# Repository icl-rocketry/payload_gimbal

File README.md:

# payload_gimbal
the ReAL payload

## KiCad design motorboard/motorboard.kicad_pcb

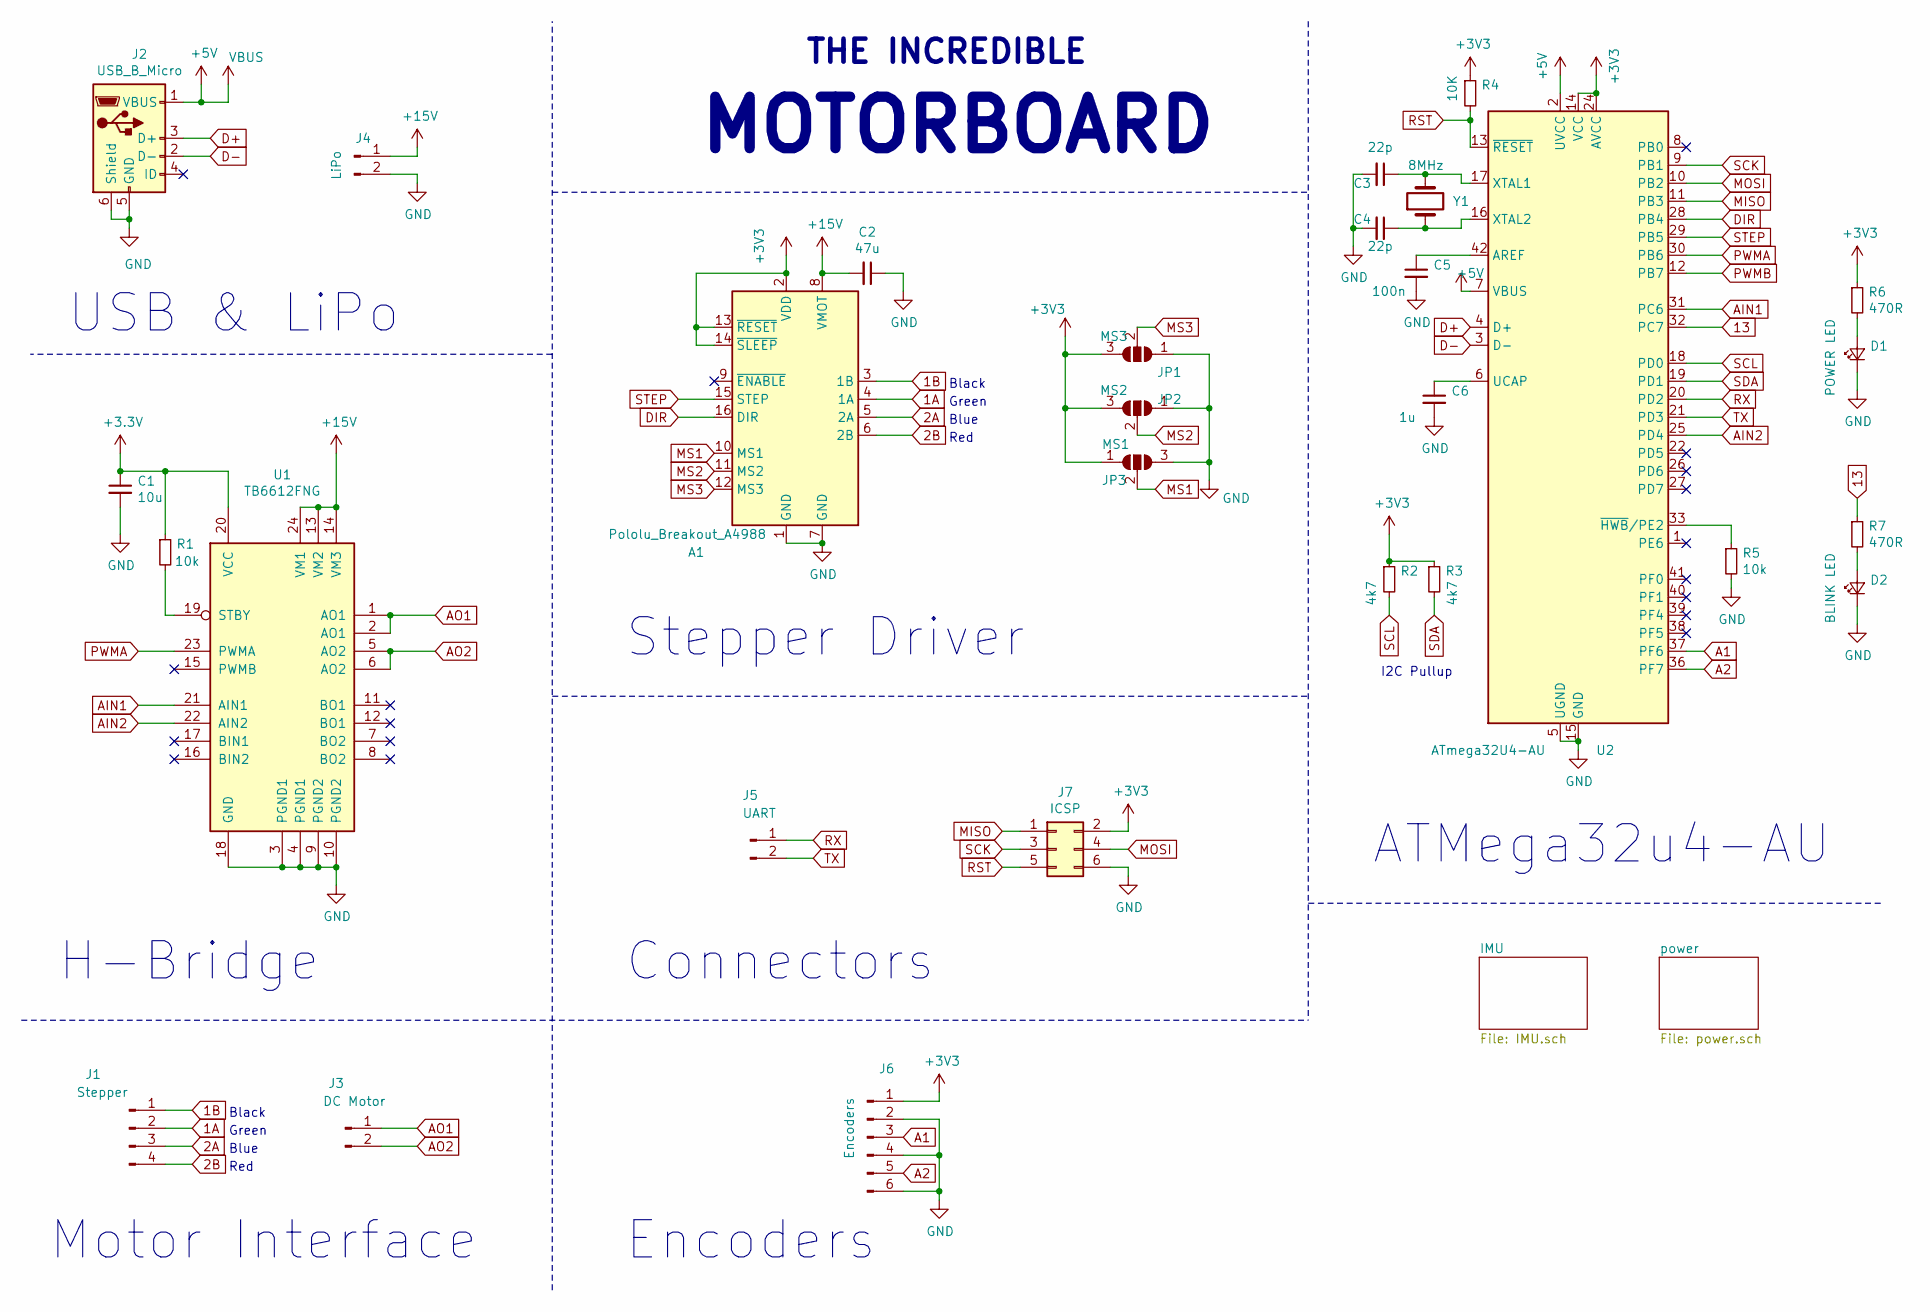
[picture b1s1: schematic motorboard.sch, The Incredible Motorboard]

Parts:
A1: Pololu_Breakout_A4988; Pololu_Breakout-16_15.2x20.3mm
C1: 10u; C_0603_1608Metric
C2: 47u; C_0603_1608Metric
C3, C4: 22p; C_0603_1608Metric
C5: 100n; C_0603_1608Metric
C6: 1u; C_0603_1608Metric
D1: POWER LED; D_0603_1608Metric_Castellated
D2: BLINK LED; D_0603_1608Metric_Castellated
J1: Stepper; PinHeader_1x06_P2.54mm_Vertical
J2: USB_B_Micro; USB_Micro-B_Molex-105017-0001
J3: DC Motor; PinHeader_1x02_P2.54mm_Vertical
J4: LiPo; AMASS_XT30UPB-F_1x02_P5.0mm_Vertical
J5: UART; PinHeader_1x02_P2.54mm_Vertical
J6: Encoders; PinHeader_1x06_P2.54mm_Vertical
J7: ICSP; PinHeader_2x03_P2.54mm_Vertical
JP1: MS3; SolderJumper-3_P1.3mm_Open_RoundedPad1.0x1.5mm_NumberLabels
JP2: MS2; SolderJumper-3_P1.3mm_Open_RoundedPad1.0x1.5mm_NumberLabels
JP3: MS1; SolderJumper-3_P1.3mm_Open_RoundedPad1.0x1.5mm_NumberLabels
R1, R5: 10k; R_0603_1608Metric
R2, R3: 4k7; R_0603_1608Metric
R4: 10K; R_0603_1608Metric
R6, R7: 470R; R_0603_1608Metric
U1: TB6612FNG; SSOP-24_5.3x8.2mm_P0.65mm
U2: ATmega32U4-AU; TQFP-44_10x10mm_P0.8mm
Y1: 8MHz; Crystal_HC49-4H_Vertical

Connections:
1A: A1.4 (1A), J1.2
1B: A1.3 (1B), J1.1
2A: A1.5 (2A), J1.3
2B: A1.6 (2B), J1.4
13: R7.1, U2.32 (PC7)
+5V: J2.1 (VBUS), U2.2 (UVCC), U2.7 (VBUS); also elsewhere on the board
+15V: A1.8 (VMOT), C2.2, J4.1, U1.13 (VM2), U1.14 (VM3), U1.24 (VM1); also elsewhere on the board
A1: J6.3, U2.37 (PF6)
A2: J6.5, U2.36 (PF7)
AIN1: U1.21 (AIN1), U2.31 (PC6)
AIN2: U1.22 (AIN2), U2.25 (PD4)
AO1: J3.1, U1.1 (AO1), U1.2 (AO1)
AO2: J3.2, U1.5 (AO2), U1.6 (AO2)
D+: J2.3 (D+), U2.4 (D+)
D-: J2.2 (D-), U2.3 (D-)
DIR: A1.16 (DIR), U2.28 (PB4)
GND: A1.1 (GND), A1.7 (GND), C1.2, C2.1, C3.2, C4.2, C5.2, C6.2, D1.1 (K), D2.1 (K), J2.5 (GND), J2.6 (Shield), J4.2, J6.2, J6.4, J6.6, J7.6, JP1.1 (A), JP2.1 (A), JP3.3 (B), R5.2, U1.3 (PGND1), U1.4 (PGND1), U1.9 (PGND2), U1.10 (PGND2), U1.18 (GND), U2.5 (UGND), U2.15 (GND), U2.23 (GND), U2.35 (GND), U2.43 (GND); also elsewhere on the board
MISO: J7.1, U2.11 (PB3)
MOSI: J7.4, U2.10 (PB2)
MS1: A1.10 (MS1), JP3.2 (C)
MS2: A1.11 (MS2), JP2.2 (C)
MS3: A1.12 (MS3), JP1.2 (C)
unnamed: C3.1, U2.17 (XTAL1), Y1.2
unnamed: C4.1, U2.16 (XTAL2), Y1.1
unnamed: C5.1, U2.42 (AREF)
unnamed: C6.1, U2.6 (UCAP)
unnamed: D1.2 (A), R6.2
unnamed: D2.2 (A), R7.2
unnamed: R1.2, U1.19 (STBY)
unnamed: R5.1, U2.33 (~HWB~/PE2)
PWMA: U1.23 (PWMA), U2.30 (PB6)
PWMB: U2.12 (PB7)
RST: J7.5, R4.2, U2.13 (~RESET)
RX: J5.1, U2.20 (PD2)
SCK: J7.3, U2.9 (PB1)
SCL: R2.2, U2.18 (PD0); also elsewhere on the board
SDA: R3.2, U2.19 (PD1); also elsewhere on the board
STEP: A1.15 (STEP), U2.29 (PB5)
TX: J5.2, U2.21 (PD3)

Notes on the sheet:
H-Bridge
USB & LiPo
ATMega32u4-AU
Motor Interface
Encoders
MOTORBOARD
THE INCREDIBLE
I2C Pullup
Stepper Driver
Black
Green
Blue
Red
Connectors

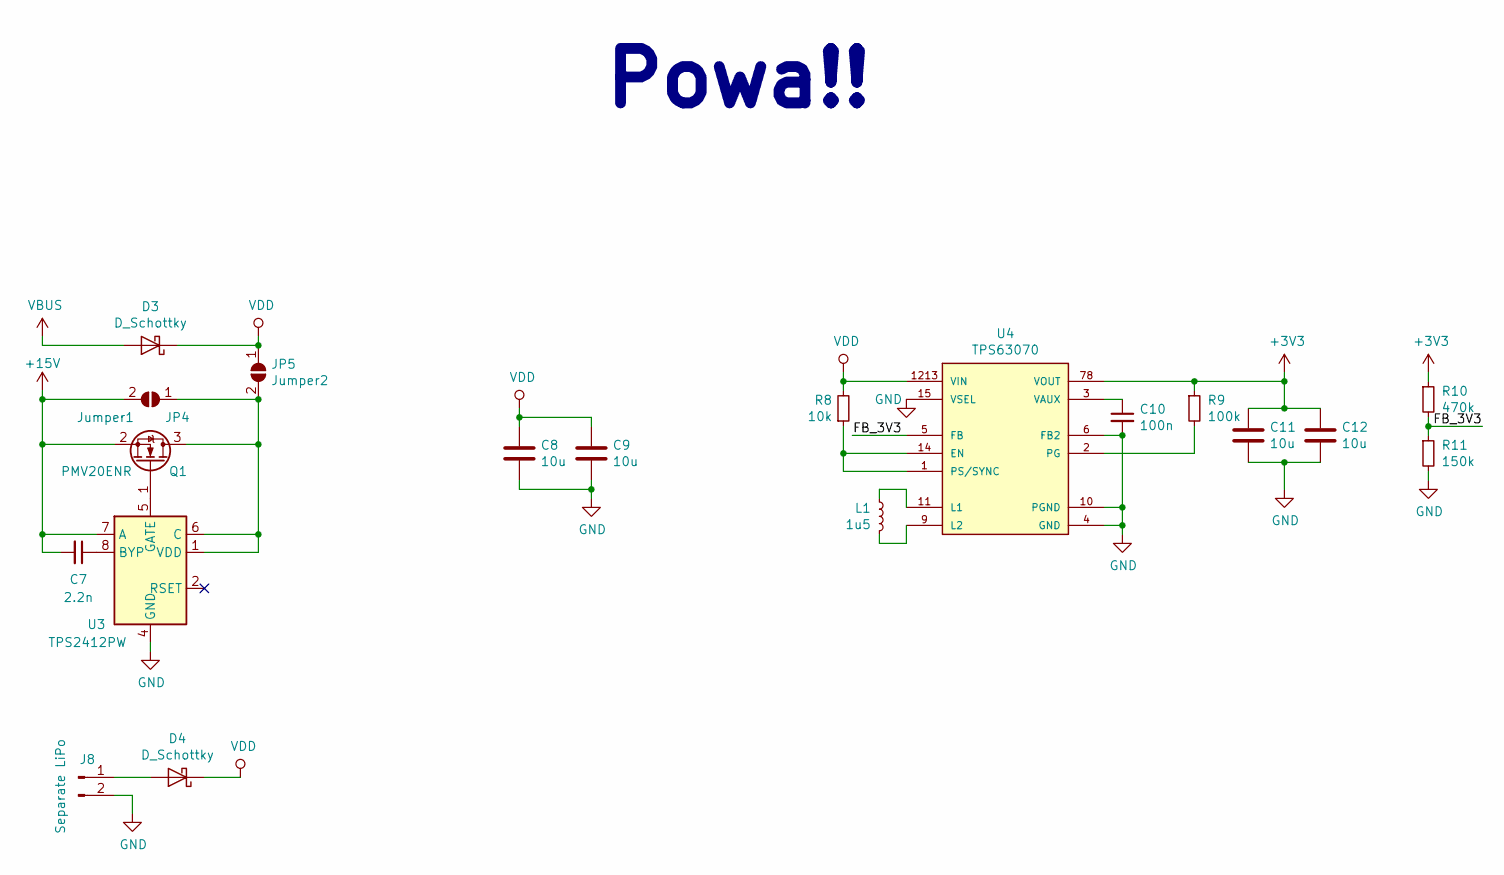
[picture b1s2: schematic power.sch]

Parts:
C7: 2.2n; C_0603_1608Metric
C8, C9, C11, C12: 10u; C_0603_1608Metric
C10: 100n; C_0603_1608Metric
D3, D4: D_Schottky; D_SOD-123F
J8: Separate LiPo; PinHeader_1x02_P2.54mm_Vertical
JP4: Jumper1; SolderJumper-2_P1.3mm_Open_RoundedPad1.0x1.5mm
JP5: Jumper2; SolderJumper-2_P1.3mm_Open_RoundedPad1.0x1.5mm
L1: 1u5; L_Taiyo-Yuden_NR-30xx
Q1: PMV20ENR; SOT-23
R8: 10k; R_0603_1608Metric
R9: 100k; R_0603_1608Metric
R10: 470k; R_0603_1608Metric
R11: 150k; R_0603_1608Metric
U3: TPS2412PW; TSSOP-8_4.4x3mm_P0.65mm
U4: TPS63070; Texas_PowerVFQFN_15

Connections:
+5V: D3.2 (A); also elsewhere on the board
+15V: C7.2, JP4.2 (B), Q1.2 (S), U3.7 (A); also elsewhere on the board
/power/FB_3V3: R10.2, R11.1, U4.5 (FB)
GND: C8.2, C9.2, C10.2, C11.2, C12.2, J8.2, R11.2, U3.3 (GND), U3.4 (GND), U4.4 (GND), U4.6 (FB2), U4.10 (PGND), U4.15 (VSEL); also elsewhere on the board
unnamed: C7.1, U3.8 (BYP)
unnamed: C10.1, U4.3 (VAUX)
unnamed: D4.2 (A), J8.1
unnamed: JP4.1 (A), JP5.2 (B), Q1.3 (D), U3.1 (VDD), U3.6 (C)
unnamed: L1.1, U4.9 (L2)
unnamed: L1.2, U4.11 (L1)
unnamed: Q1.1 (G), U3.5 (GATE)
unnamed: R8.1, U4.1 (PS/SYNC), U4.14 (EN)
unnamed: R9.2, U4.2 (PG)
VDD: C8.1, C9.1, D3.1 (K), D4.1 (K), JP5.1 (A), R8.2, U4.1213 (VIN)

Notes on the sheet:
Powa!!

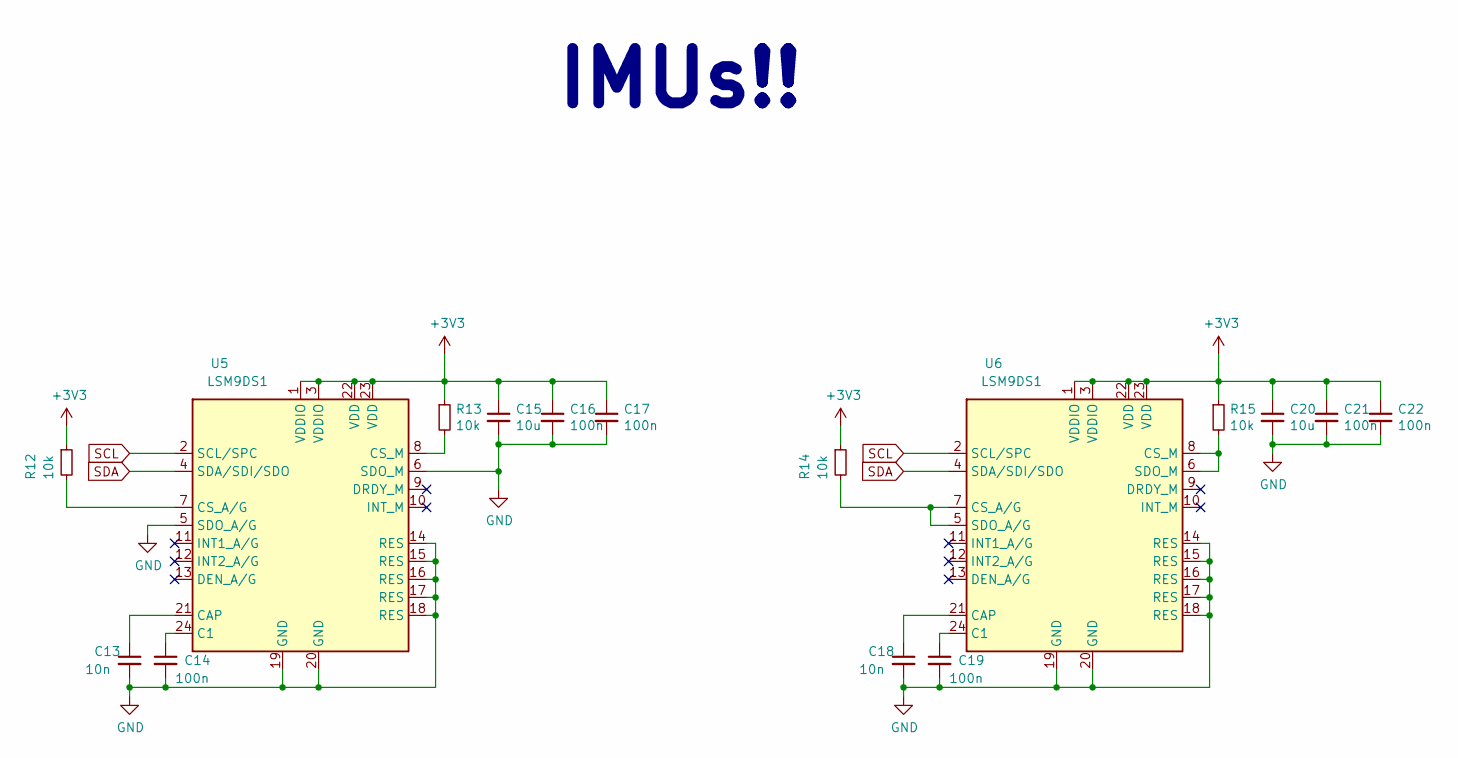
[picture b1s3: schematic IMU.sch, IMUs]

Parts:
C13, C18: 10n; C_0603_1608Metric
C14, C16, C17, C19, C21, C22: 100n; C_0603_1608Metric
C15, C20: 10u; C_0603_1608Metric
R12, R13, R14, R15: 10k; R_0603_1608Metric
U5, U6: LSM9DS1; LGA-24L_3x3.5mm_P0.43mm

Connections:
GND: C13.2, C14.2, C15.2, C16.2, C17.2, C18.2, C19.2, C20.2, C21.2, C22.2, U5.5 (SDO_A/G), U5.6 (SDO_M), U5.14 (RES), U5.15 (RES), U5.16 (RES), U5.17 (RES), U5.18 (RES), U5.19 (GND), U5.20 (GND), U6.14 (RES), U6.15 (RES), U6.16 (RES), U6.17 (RES), U6.18 (RES), U6.19 (GND), U6.20 (GND); also elsewhere on the board
unnamed: C13.1, U5.21 (CAP)
unnamed: C14.1, U5.24 (C1)
unnamed: C18.1, U6.21 (CAP)
unnamed: C19.1, U6.24 (C1)
unnamed: R12.2, U5.7 (CS_A/G)
unnamed: R13.2, U5.8 (CS_M)
unnamed: R14.2, U6.5 (SDO_A/G), U6.7 (CS_A/G)
unnamed: R15.2, U6.6 (SDO_M), U6.8 (CS_M)
SCL: U5.2 (SCL/SPC), U6.2 (SCL/SPC); also elsewhere on the board
SDA: U5.4 (SDA/SDI/SDO), U6.4 (SDA/SDI/SDO); also elsewhere on the board

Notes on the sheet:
IMUs!!

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
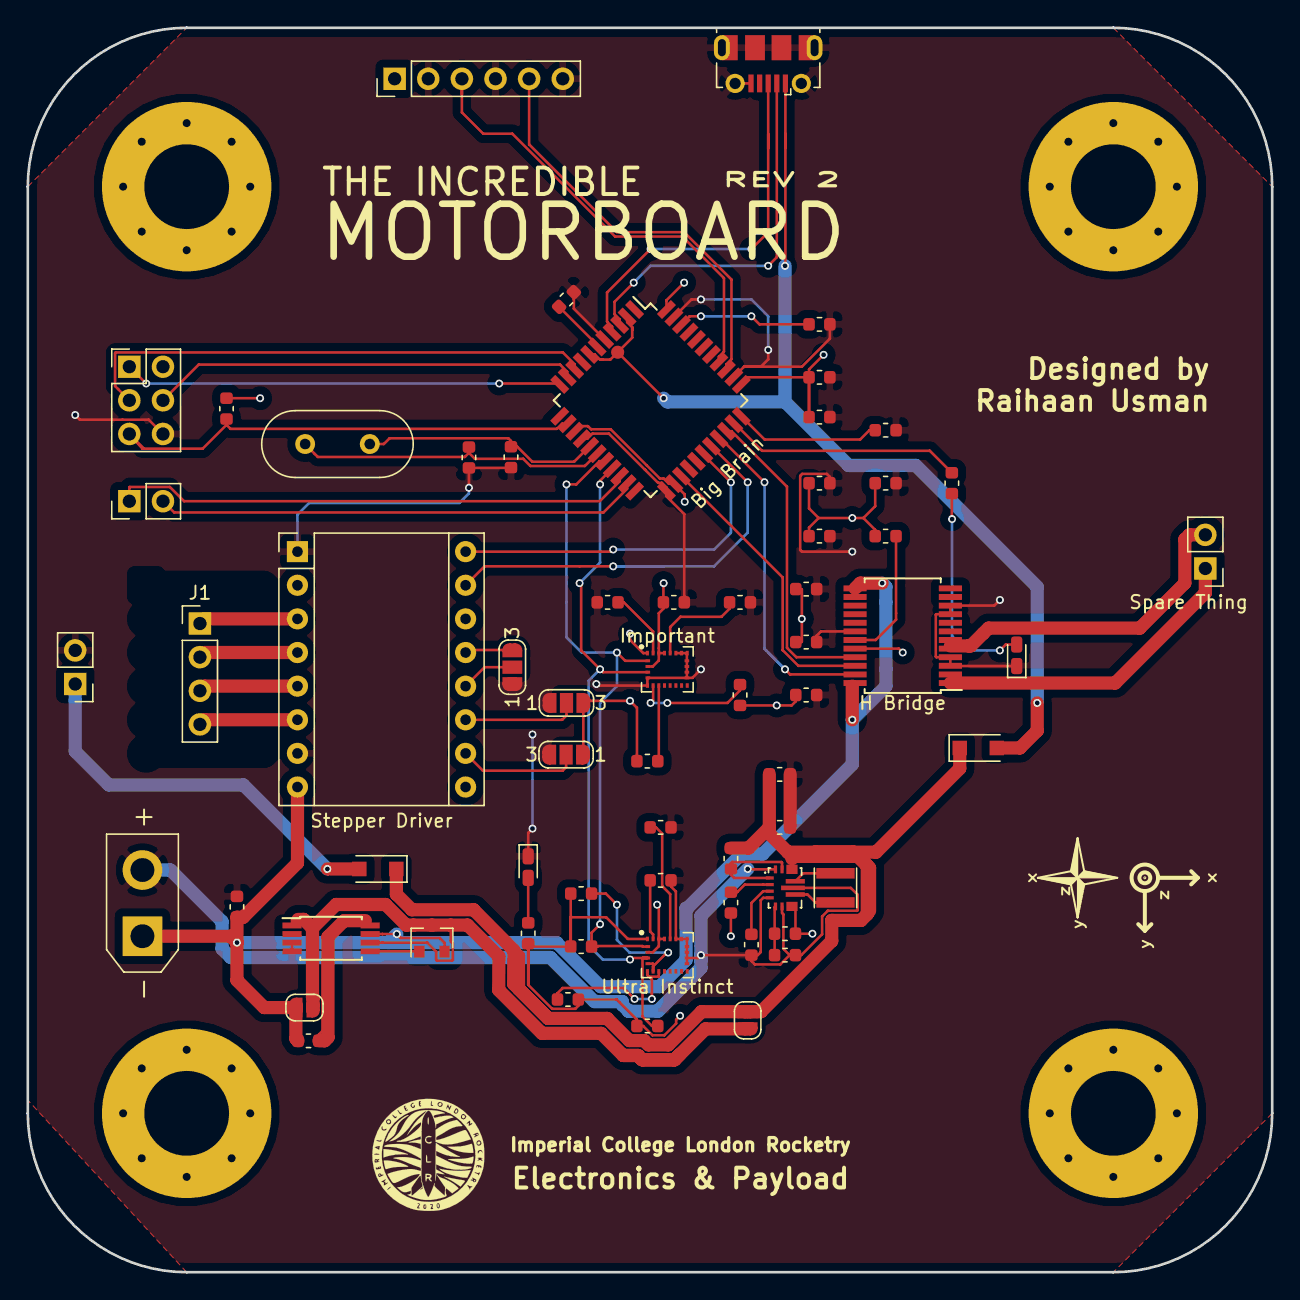
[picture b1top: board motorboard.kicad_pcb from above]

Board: 2 copper layers, 94.0 x 94.0 mm, 68 parts (0 on the bottom side), 58 nets.

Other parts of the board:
BottomLeft: A_Hole; MountingHole_6.4mm_M6_Pad_Via
TopLeft: Hi; MountingHole_6.4mm_M6_Pad_Via
TopRight: Bye; MountingHole_6.4mm_M6_Pad_Via
e: Yeet; MountingHole_6.4mm_M6_Pad_Via

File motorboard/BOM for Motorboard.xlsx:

Id | Designator | Package | Quantity | Designation | Unit Price | Farnell Order Code | Digikey Part Nr | URL | Total Price
4 | Y1 | Crystal_HC18-U_Vertical | 1 | 8MHz | 0.35099999999999998 | 1842268 |  | https://uk.farnell.com/txc/9b-8-000maaj-b/xtal-8-000mhz-18pf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 | 0.35099999999999998
9 | U2 | TQFP-44_10x10mm_P0.8mm | 1 | ATmega32U4-AU | 3.17 | 1748525 |  | https://uk.farnell.com/microchip/atmega32u4-au/mcu-8bit-mega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 | 3.17
12 | J2 | USB_Micro-B_Molex-105017-0001 | 1 | USB_B_Micro | 0.66900000000000004 | 2293836 |  | https://uk.farnell.com/molex/105017-0001/usb-conn-2-0-micro-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 | 0.66900000000000004
13 | U6,U5 | LGA-24L_3x3.5mm_P0.43mm | 2 | LSM9DS1 | 5.26 | 2532383 |  | https://uk.farnell.com/stmicroelectronics/lsm9ds1tr/mems-acc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 | 10.52
14 | U4 | Texas_PowerVFQFN_15 | 1 | TPS63070 | 2.2599999999999998 | 3007465 |  | https://uk.farnell.com/texas-instruments/tps63070rnmr/dc-dc-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 | 2.2599999999999998
15 | U3 | TSSOP-8_4.4x3mm_P0.65mm | 1 | TPS2412PW | 2.4700000000000002 | 2383048 |  | https://uk.farnell.com/texas-instruments/tps2412pw/o-ring-co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 | 2.4700000000000002
16 | U1 | SSOP-24_5.3x8.2mm_P0.65mm | 1 | TB6612FNG |  |  |  |  | 0
17 | R15,R14,R13,R12,R8,R5,R1 | R_0603_1608Metric | 7 | 10k | 1.37E-2 | 1469748RL |  | https://uk.farnell.com/vishay/crcw060310k0fkea/res-10k-1-0-1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 | 9.5899999999999999E-2
18 | R11 | R_0603_1608Metric | 1 | 150k | 1.37E-2 | 1469759 |  | https://uk.farnell.com/vishay/crcw0603150kfkea/res-150k-1-0-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 | 1.37E-2
19 | R10 | R_0603_1608Metric | 1 | 470k | 0.30299999999999999 | 2331232 |  | https://uk.farnell.com/te-connectivity/cpf0603b470ke1/res-47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 | 0.30299999999999999
20 | R9 | R_0603_1608Metric | 1 | 100k | 2.5899999999999999E-2 | 9234250 |  | https://uk.farnell.com/yageo/rc0805jr-07100kl/res-100k-5-0-1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 | 2.5899999999999999E-2
21 | R7,R6 | R_0603_1608Metric | 2 | 470R | 1.77E-2 | 9233334 |  | https://uk.farnell.com/yageo/rc0603jr-07470rl/res-470r-5-0-1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 | 3.5400000000000001E-2
22 | R4 | R_0603_1608Metric | 1 | 10K | 1.37E-2 | 1469748RL |  | https://uk.farnell.com/vishay/crcw060310k0fkea/res-10k-1-0-1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 | 1.37E-2
23 | R3,R2 | R_0603_1608Metric | 2 | 4k7 | 0.28100000000000003 | 1577615 |  | https://uk.farnell.com/panasonic/era3aeb472v/res-4k7-0-1-0-1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 | 0.56200000000000006
24 | Q1 | SOT-23 | 1 | PMV20ENR | 0.3 |  | 1727-2301-1-ND | https://www.digikey.co.uk/product-detail/en/nexperia-usa-inc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 | 0.3
25 | L1 | L_Taiyo-Yuden_NR-30xx | 1 | 1u5 | 0.153 | 2211176 |  | https://uk.farnell.com/tdk/c1608x5r1e155k080ab/cap-1-5-f-25v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 | 0.153
37 | D4,D3 | D_SOD-123F | 2 | D_Schottky | 0.12 |  | 1655-1926-1-ND | https://www.digikey.co.uk/product-detail/en/smc-diode-soluti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 | 0.24
40 | C22,C21,C19,C17,C16,C14,C10,C5 | C_0603_1608Metric | 10 | 100n | 4.9000000000000002E-2 | 1657913 |  | https://uk.farnell.com/avx/02016d104kat2a/cap-0-1-f-6-3v-10-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 | 0.49
41 | C20,C15,C12,C11,C9,C8,C1 | C_0603_1608Metric | 10 | 10u | 0.122 | 2456110 |  | https://uk.farnell.com/murata/grm188r61a106me69d/cap-10-f-10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 | 1.22
42 | C18,C13 | C_0603_1608Metric | 10 | 10n | 4.1300000000000003E-2 | 1657919 |  |  | 0.41300000000000003
43 | C7 | C_0603_1608Metric | 10 | 2.2n | 8.0699999999999994E-2 | 1658869 |  | https://uk.farnell.com/avx/06035c223kat2a/cap-0-022-f-50v-10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 | 0.80699999999999994
44 | C6 | C_0603_1608Metric | 10 | 1u | 8.4500000000000006E-2 | 2470448 |  | https://uk.farnell.com/murata/grm033r60j105mea2d/cap-1-f-6-3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 | 0.84500000000000008
45 | C4,C3 | C_0603_1608Metric | 10 | 22p | 1.5599999999999999E-2 | 2434636 |  | https://uk.farnell.com/murata/grm0335c1e220ja01d/cap-22pf-25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 | 0.156
46 | C2 | C_0603_1608Metric | 5 | 47u | 0.91300000000000003 | 1572633 |  | https://uk.farnell.com/kemet/c0805c476m9pactu/cap-47-f-6-3v-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 | 4.5650000000000004
 |  |  |  |  |  |  |  | Total | 29.678599999999992

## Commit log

2020-01-30 a new begining
2020-01-30 1st commit
2020-01-30 update test
2020-01-30 Still testing
2020-01-31 Completed power things
2020-01-31 Arduino is set up
2020-01-31 h bridge started
2020-01-31 basic h bridge complete
2020-02-02 Switched to TB6612
2020-02-02 H-bridge setup complete
2020-02-02 Encoder started
2020-02-04 Replaced ATMega328
2020-02-09 update 09/02
2020-02-12 Complete - Rev1
2020-02-12 nearrrly there
2020-02-13 tidying things
2020-02-13 neater
2020-02-14 Debugged
    *Should* work
2020-02-16 PCB build started
2020-02-19 Sad day for GitHub
2020-02-19 GitHub works again!
2020-02-20 PCB nearly done!
2020-02-20 Literally the last few nets...
2020-02-20 It broke again
2020-02-20 basically done
2020-02-21 ready for fab
2020-02-22 Added BOM
2020-03-11 neater again!
2020-03-19 noob error fixed
2020-03-19 tweaks
2020-03-20 forgot something crucial...
2020-03-20 Stepper test sketch added
2020-03-20 moved things around, looks cleaner
2020-03-26 rev2 started
2020-03-26 nicer board!
2020-03-26 Rev2 complete
2020-03-26 4 pin header for stepper
2020-03-31 edit
